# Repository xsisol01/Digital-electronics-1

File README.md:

# Digital-electronics-1
## Labs
*hello hello*
~~chyba~~

Meno|Priezvisko
------- | -------
Filip|Sisolak

**Source code**

```vhdl
architecture data flow 
```

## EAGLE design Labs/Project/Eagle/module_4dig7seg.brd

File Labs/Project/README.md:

# Door lock system with PIN (4-digit) terminal, 4x3 push buttons, 4-digit 7-segment display, relay for door lock control.

### Team members
* Bohuslav Šotola
* Tomáš Škurla
* Barbora Šimková
* Filip Šišolák

Github repository link : https://github.com/xsisol01/Digital-electronics-1/tree/main/Labs

### Project objectives
The scope of this project was to create the lock system utilizing an Arty A7-100T board. The project, as per the initial assignment, consists of a 4x3 keypad, a 4-digit 7segment display, and a relay to control the door lock. We also implemented a Three-color-LED whose colors represent each state of the door ( Green for Opened, Red for Closed). The 4-digit 7 segment display is located on a breadboard connected to the board via Pmod connectors.

### Hardware description
Hardware used in this project:
* Arty A7-100T board (https://www.robotshop.com/eu/en/arty-a7-100t-artix-7-fpga-development-board.html)
* Pmod SSR: Solid State Relay Electronic Switch (https://store.digilentinc.com/pmod-ssr-solid-state-relay-electronic-switch/)
* Membrane 3x4 Matrix Keypad (https://www.adafruit.com/product/419)
* Custom 4 Digit 7 segment module 

#### Table with pinouts for used modules
##### Table for Keypad control module
| General purpose I/O pins | 
|      :--------:          | 
|    I40     | 
|    I39     | 
|    I38     | 
|    I37     | 
|    I36     | 
|    I35     | 
|    I34     | 
##### Table for 7 seg 4 digits module 
| Pmod JB | Connection | Cathodes | Pmod JC | Connection | Anodes |
| :-----: | :--------: | :------: | :-----: | :--------: | :----: |
|  Pin 1  |    E15     |    CA    |  Pin 1  |    U12     |  AN0   |
|  Pin 2  |    E16     |    CB    |  Pin 2  |    V12     |  AN1   |
|  Pin 3  |    D15     |    CC    |  Pin 3  |    V10     |  AN2   |
|  Pin 4  |    C15     |    CD    |  Pin 4  |    V11     |  AN3   |
|  Pin 7  |    J17     |    CE    |  Pin 7  |    U14     |   -    |
|  Pin 8  |    J18     |    CF    |  Pin 8  |    V14     |   -    |
|  Pin 9  |    K15     |    CG    |  Pin 9  |    T13     |   -    |
| Pin 10  |    J15     |    DP    | Pin 10  |    U13     |   -    |

##### Table for Relay module
| Pmod JA | Connection | 
| :-----: | :--------: | 
|  Pin 1  |    G13     | 
|  Pin 2  |    B11     | 
|  Pin 3  |    A11     | 
|  Pin 4  |    D12     | 
|  Pin 7  |    D13     | 
|  Pin 8  |    B18     | 
|  Pin 9  |    A18     | 
| Pin 10  |    K16     | 

#### Theoretical imagine of all of modules connected together 

### VHDL modules description and simulations
* [4x3 KeyPad control module](https://github.com/xsisol01/Digital-electronics-1/tree/main/Labs/Project#keypad-control-module) 
* [Relay control module](https://github.com/xsisol01/Digital-electronics-1/tree/main/Labs/Project#relay-control-module)
* [7seg display control module](https://github.com/xsisol01/Digital-electronics-1/tree/main/Labs/Project#driver-for-multiple-seven-segment-displays)
* [Lock logic module](https://github.com/xsisol01/Digital-electronics-1/tree/main/Labs/Project#lock-logic-module)
* [Top module](https://github.com/xsisol01/Digital-electronics-1/tree/main/Labs/Project#top-module-description-and-simulations)

## KeyPad control module
### Description
Module "keypad_to_num" for controlling 4x3 keypad contains from 3 input ports -> clk (needed to control state machine), reset (which is not needed in this case, but we are using template from previous labs), row_i (where comes the inforamtion which key was pressed). There are also 2 output ports -> col_o (sending sequention of 0 and 1 to the keypad columns) and finally the num_o (which send bin signal representing pressed key on keypad).
Keypad_to_num works on basis of state machine where each state change to another after defined time.
Each key represent bin signal - same as the label of the button on keypad for example 7 means b"0111". All other combinations are in table.

##### Functionality 

##### Table - Key pressed on keypad => num_o
| Key | num_o | Value |
| :-: | :-: | :-: | 
| 0 | b"0000" | 0 | 
| 1 | b"0001" | 1 | 
| 2 | b"0010" | 2 | 
| 3 | b"0011" | 3 | 
| 4 | b"0100" | 4 | 
| 5 | b"0101" | 5 | 
| 6 | b"0110" | 6 | 
| 7 | b"0111" | 7 | 
| 8 | b"1000" | 8 |  
| 9 | b"1001" | 9 | 
| * | b"1110" | DELETE | 
| # | b"1111" | ENTER |
| N/A | b"1101" | DEFAULT | 

##### State diagram 

### VHDL code and simulation
##### VHDL code of KeyPad controller - `keypad_to_num.vhdl`
[Link to `keypad_to_num.vhdl`](https://github.com/xsisol01/Digital-electronics-1/blob/main/Labs/Project/Lock/project_final2.srcs/sources_1/imports/Project/Project_lock/Project_lock.srcs/sources_1/new/keypad_to_num.vhd)

```vhdl
library ieee;
use ieee.std_logic_1164.all;
use ieee.numeric_std.all;

------------------------------------------------------------------------
-- Entity declaration for traffic light controller
------------------------------------------------------------------------
entity keypad_to_num is
    port(
        clk         : in  std_logic;
        reset       : in  std_logic;
        row_i       : in  std_logic_vector(4 - 1 downto 0);     -- input from keypad
        
        col_o       : out std_logic_vector(3 - 1 downto 0);     -- output to keypad
        num_o       : out std_logic_vector(4 - 1 downto 0)      --Output signal with 4bit number 0-9, enter, delete
        
    );
end entity keypad_to_num;

------------------------------------------------------------------------
-- Architecture declaration for traffic light controller
------------------------------------------------------------------------
architecture Behavioral of keypad_to_num is

    -- Define the states
    type t_state is (SET_COLH,      --after reset
                     SET_COL1,
                     SET_COL2,
                     SET_COL3
                     );
        
    -- Define the signal that uses different states
    signal s_state  : t_state;
    -- Internal clock enable
    signal s_en     : std_logic; --not needed in this case
    -- Local delay counter
    signal   s_cnt  : unsigned(5 - 1 downto 0);

    constant c_DELAY_100ms : unsigned(5 - 1 downto 0) := b"0_0010"; --one pulse every 100ms
    constant c_ZERO        : unsigned(5 - 1 downto 0) := b"0_0000";

begin

    clk_en0 : entity work.clock_enable
        generic map(
            g_MAX => 5000000       -- g_MAX = 50 ms / (1/100 MHz) 
        )
        port map(
            clk   => clk,
            reset => reset,
            ce_o  => s_en
        );

    --Process sensitive to clock change, defining state machine rules
    p_in_to_num_out : process(clk)
    begin
        if rising_edge(clk) then
            if (reset = '1') then          -- Synchronous reset
                s_state <= SET_COLH ;      -- Set initial state
                --s_cnt <= c_ZERO;

            elsif (s_en = '1') then
            
                case s_state is
                    when SET_COLH =>
                        if (s_cnt < c_DELAY_100ms) then
                            s_cnt <= s_cnt + 1;   
                        else
                            s_state <= SET_COL1;
                            s_cnt <= c_ZERO;
                        end if;
                        
                    when SET_COL1 =>
                        if (s_cnt < c_DELAY_100ms) then
                            s_cnt <= s_cnt + 1;
                        else
                            s_state <= SET_COL2;
                            s_cnt <= c_ZERO;
                       end if;
                           
                    when SET_COL2 =>
                        if (s_cnt < c_DELAY_100ms) then
                            s_cnt <= s_cnt + 1; 
                        else
                            s_state <= SET_COL3;
                            s_cnt <= c_ZERO;
                        end if;
                        
                    when SET_COL3 =>
                        if (s_cnt < c_DELAY_100ms) then
                            s_cnt <= s_cnt + 1; 
                        else
                            s_state <= SET_COL1;
                            s_cnt <= c_ZERO;
                        end if; 
                           
                    when others =>
                        s_state <= SET_COLH;                   
               end case;            
            end if; -- Synchronous reset
        end if; -- Rising edge
    end process p_in_to_num_out;

    --Process senstitive on current state and setting output to columns
    p_output_statechanger : process(s_state)
    begin
        case s_state is
            when SET_COLH =>
                col_o <= "111";   
            when SET_COL1 =>
                col_o <= "011";    
            when SET_COL2 =>
                col_o <= "101";     
            when SET_COL3 =>
                col_o <= "110";
            when others =>
                col_o <= "111";
        end case;
    end process p_output_statechanger;

    --Process sensitive to row_i changes and setting output based on current state
    p_output_row_check_out : process(row_i)
    begin
        case s_state is
            when SET_COLH =>
                num_o <= "1101";                -- default
                
            when SET_COL1 =>
                if(row_i = "0111") then
                    num_o <= "0001";            --set output 1 - pressed
                               
                elsif(row_i = "1011") then  
                    num_o <= "0100";            --set output 4 - pressed
                                
                elsif(row_i = "1101") then  
                    num_o <= "0111";            --set output 7 - pressed  
                                
                elsif(row_i = "1110") then  
                    num_o <= "1110";            --set output *(delete) - pressed
                else 
                    num_o <= "1101";            --defult            
                end if;
                
            when SET_COL2 =>
                if(row_i = "0111") then
                    num_o <= "0010";            --set output 2 - pressed
                            
                elsif(row_i = "1011") then  
                    num_o <= "0101";            --set output 5 - pressed
                            
                elsif(row_i = "1101") then  
                     num_o <= "1000";           --set output 8 - pressed  
                            
                elsif(row_i = "1110") then  
                     num_o <= "0000";           --set output 0 - pressed 
                else 
                     num_o <= "1101";           --defult no output          
                end if;
                
            when SET_COL3 =>
                if(row_i = "0111") then
                     num_o <= "0011";           --set output 3 - pressed
                                
                elsif(row_i = "1011") then  
                     num_o <= "0110";           --set output 6 - pressed
                                
                elsif(row_i = "1101") then  
                       num_o <= "1001";         --set output 9 - pressed  
                                
                elsif(row_i = "1110") then  
                       num_o <= "1111";         --set output #(enter) - pressed
                else 
                     num_o <= "1101";           --defult         
                end if; 
                
            when others =>
                num_o <= "1101";
          end case;
      end process p_output_row_check_out;  
end architecture Behavioral;
```

##### Simulation of KeyPad controller - `tb_keypad_to_num.vhdl`
[Link to `tb_keypad_to_num.vhdl`](https://github.com/xsisol01/Digital-electronics-1/blob/main/Labs/Project/Lock/project_final2.srcs/sim_1/new/tb_keypad_to_num.vhd)

```vhdl
library ieee;
use ieee.std_logic_1164.all;

entity tb_keypad_to_num is
    -- Entity of testbench is always empty
end entity tb_keypad_to_num;

architecture testbench of tb_keypad_to_num is

    -- Local constants
    constant c_CLK_100MHZ_PERIOD : time := 10 ns;

    --Local signals
    signal s_clk_100MHz : std_logic;
    signal s_reset      : std_logic;
    signal s_row        : std_logic_vector(4 - 1 downto 0);
    signal s_col        : std_logic_vector(3 - 1 downto 0);
    signal s_num        : std_logic_vector(4 - 1 downto 0);

begin

    uut_tlc : entity work.keypad_to_num
        port map(
            clk     => s_clk_100MHz,
            reset   => s_reset, 
            row_i   => s_row,
            col_o   => s_col,
            num_o   => s_num
        );

    p_clk_gen : process
    begin
        while now < 800 ms loop   
            s_clk_100MHz <= '0';
            wait for c_CLK_100MHZ_PERIOD / 2;
            s_clk_100MHz <= '1';
            wait for c_CLK_100MHZ_PERIOD / 2;
        end loop;
        wait;
    end process p_clk_gen;

    p_stimulus : process
    begin
    
        s_row <= "1111";  
        wait for 57 ms;
    
        s_row <= "0111";
        wait for 50 ms; 
        
        s_row <= "1111";  
        wait for 157 ms; 
        
        s_row <= "1101";
        wait for 52 ms;
        
        s_row <= "1111";  
        wait for 157 ms; 
        
        s_row <= "1011";
        wait for 52 ms;

        s_row <= "1111";  
        wait;
    end process p_stimulus;

end architecture testbench;  
```

##### Image of simulation waveforms - simulating KeyPad controller module

## Relay control module
### Description
In this project there is also a solid state relay which is connected to the board via Pmod (JA) connectors. I use a two – state diagram: Close_door (default state) and Open_door.

If keypad_i = ‘1’ the Close_door will be changed to state Open_door. Signal s_keypad is coming from module locker_logic.

If keypad_i = ‘0’ the Close_door will be still closed.

Solid state relay uses six pins, but only three are used, namely: Pin 1 (ON), Pin 5 (GND) and Pin 6 (VCC  3.3/5V).

STATES:

Open_door:

door_o = ‘1’  //door is opened

LED_o = “010” // LED color is green

Close_door:

door_o = ‘0’  //door is closed

LED_o = “100”// LED color is red

### Functionality 

### State Diagram

### VHDL code and simulation
#### VHDL code of Relay controller - `relay_to_door.vhdl`
[Link to `relay_to_door.vhdl`](https://github.com/xsisol01/Digital-electronics-1/blob/main/Labs/Project/Lock/project_final2.srcs/sources_1/new/relay_to_door.vhd)

```vhdl
library ieee;
use ieee.std_logic_1164.all;
use ieee.numeric_std.all;

entity relay_to_door is
    port(
       keypad_i     : in  std_logic;
        clk          : in  std_logic;
        reset        : in  std_logic;
        
        door_o      : out  std_logic; 
        LED_o : out std_logic_vector(3 - 1 downto 0)

    );
end entity relay_to_door;

architecture Behavioral of relay_to_door is

    type   t_state is (close_door, open_door);                   
    signal s_state  : t_state;

    signal s_en             : std_logic;
    signal s_keypad         : std_logic;

    signal   s_cnt  : unsigned(5 - 1 downto 0);

    constant c_DELAY_7SEC : unsigned(5 - 1 downto 0) := b"1_1100";
    constant c_DELAY_3SEC : unsigned(5 - 1 downto 0) := b"0_1100";
    constant c_DELAY_1SEC : unsigned(5 - 1 downto 0) := b"0_0100";
    constant c_ZERO       : unsigned(5 - 1 downto 0) := b"0_0000";

begin
    
    s_en <= '1';

 p_state_changer : process(clk,reset,keypad_i)
    begin
        if rising_edge(clk) then
            if (reset = '1') then     
                s_state <= close_door ;     
                s_cnt <= c_ZERO;

            elsif (s_en = '1') then
            
                case s_state is
                    when close_door =>
                        if (keypad_i = '1') then
                            s_state <= open_door;
                            s_cnt   <= c_ZERO;  
                        else
                            s_state <= close_door;
                            s_cnt <= c_ZERO;
                        end if;
                        
                    when open_door =>
                        if (s_cnt < c_DELAY_7SEC) then
                            s_cnt <= s_cnt + 1;
                        else
                            s_state <= close_door;
                            s_cnt <= c_ZERO;
                       end if;
                                  
                    when others =>
                        s_state <= close_door;                   
               end case;            
            end if;
        end if; 
    end process p_state_changer;

    p_output_door : process(s_state)
    begin
        case s_state is

            when close_door =>
                LED_o <= "100";
                door_o <='0';
                
            when open_door =>
                LED_o <= "010";   
                door_o <='1';
           
        end case;
    end process p_output_door;

end architecture Behavioral;

```

#### Simulation of Relay control - `tb_relay_to_door.vhdl`
[Link to `tb_relay_to_door.vhdl`](https://github.com/xsisol01/Digital-electronics-1/blob/main/Labs/Project/Lock/project_final2.srcs/sim_1/new/tb_relay_to_door.vhd)

```vhdl
library ieee;
use ieee.std_logic_1164.all;

entity tb_relay_to_door is
    -- Entity of testbench is always empty
end entity tb_relay_to_door;

architecture testbench of tb_relay_to_door is

    constant c_CLK_100MHZ_PERIOD : time := 10 ns;

    --Local signals
    signal s_clk_100MHz : std_logic;
    signal s_reset      : std_logic;
    signal s_keypad         : std_logic;
    
    signal s_LED      : std_logic_vector(3 - 1 downto 0);

begin
    uut_relay_to_door : entity work.relay_to_door
        port map(
            clk     => s_clk_100MHz,
            reset   => s_reset,
            keypad_i =>s_keypad,
            LED_o => s_LED

        );

    p_clk_gen : process
    begin
        while now < 10000 ns loop 
            s_clk_100MHz <= '0';
            wait for c_CLK_100MHZ_PERIOD / 2;
            s_clk_100MHz <= '1';
            wait for c_CLK_100MHZ_PERIOD / 2;
        end loop;
        wait;
    end process p_clk_gen;

    p_reset_gen : process
    begin
        s_reset <= '0';
        s_keypad <= '1'; wait for 200ns;
        s_keypad <= '0';wait for 100ns;
        s_keypad <= '1';
        wait;
    end process p_reset_gen;

    p_stimulus : process
    begin
        
        wait;
    end process p_stimulus;

end architecture testbench;

```
#### Image of simulation waveforms

## Driver for multiple seven-segment displays

### Description
This module is used to display the numbers (PIN code) which are entered into a keypad. Module contains inputs signal such as reset, clk a four 4-bit signals data0_i, data1_i, data2_i, data3_i. Output signals are 7-bit signal seg_o and 4-bit signal dig_o. The signal seg_o determines which segment is going to light and the signal dig_o determines on which digit. The design source `clock_enable` is used to generate the clock enable signal. The design source `cnt_up_down` is binary n-bit counter and is used to counting in either direction. The design source `hex_7seg` is decoder for common anode 7-segment display.
##### Schematic of `driver_7seg_4digits` with connection to 7 segment displays

##### Schematic of 7 segment displays with connection to Arty-A7-100T

##### Board for 7 segment displays

### VHDL code and simulation

##### VHDL code of driver for 7 segment displays - `driver_7seg_4digits.vhdl`
[Link to `driver_7seg_4digits.vhdl`](https://github.com/xsisol01/Digital-electronics-1/blob/main/Labs/Project/Lock/project_final2.srcs/sources_1/new/new/driver_7seg_4digits.vhd)

```vhdl
------------------------------------------------------------------------
--
-- Copyright (c) 2020 Tomas Fryza
-- Dept. of Radio Electronics, Brno University of Technology, Czechia
-- This work is licensed under the terms of the MIT license.
--
------------------------------------------------------------------------

library ieee;
use ieee.std_logic_1164.all;
use ieee.numeric_std.all;

------------------------------------------------------------------------
-- Entity declaration for display driver
------------------------------------------------------------------------
entity driver_7seg_4digits is
    port(
        clk     : in  std_logic;        -- Main clock
        reset   : in  std_logic;        -- Synchronous reset
        -- 4-bit input values for individual digits
        data0_i : in  std_logic_vector(4 - 1 downto 0);
        data1_i : in  std_logic_vector(4 - 1 downto 0);
        data2_i : in  std_logic_vector(4 - 1 downto 0);
        data3_i : in  std_logic_vector(4 - 1 downto 0);
        -- Cathode values for individual segments
        seg_o   : out std_logic_vector(7 - 1 downto 0);
        -- Common anode signals to individual displays
        dig_o   : out std_logic_vector(4 - 1 downto 0)
    );
end entity driver_7seg_4digits;

------------------------------------------------------------------------
-- Architecture declaration for display driver
------------------------------------------------------------------------
architecture Behavioral of driver_7seg_4digits is

    -- Internal clock enable
    signal s_en  : std_logic;
    -- Internal 2-bit counter for multiplexing 4 digits
    signal s_cnt : std_logic_vector(2 - 1 downto 0);
    -- Internal 4-bit value for 7-segment decoder
    signal s_hex : std_logic_vector(4 - 1 downto 0);

begin
    --------------------------------------------------------------------
    -- Instance (copy) of clock_enable entity generates an enable pulse
    -- every 4 ms
    clk_en0 : entity work.clock_enable
        generic map(
        g_MAX => 4
        )
        port map(
         clk    => clk, 
         reset  => reset,
         ce_o   => s_en 
        );

    --------------------------------------------------------------------
    -- Instance (copy) of cnt_up_down entity performs a 2-bit down
    -- counter
    bin_cnt0 : entity work.cnt_up_down
        generic map(
        g_CNT_WIDTH => 2
        )
        port map(
        clk         => clk,   
        reset       => reset,   
        en_i        => s_en,  
        cnt_up_i    => '0',
        cnt_o       => s_cnt
        );

    --------------------------------------------------------------------
    -- Instance (copy) of hex_7seg entity performs a 7-segment display
    -- decoder
    hex2seg : entity work.hex_7seg
        port map(
            hex_i => s_hex,
            seg_o => seg_o
        );

    --------------------------------------------------------------------
    -- p_mux:
    -- A combinational process that implements a multiplexer for
    -- selecting data for a single digit, a decimal point signal, and 
    -- switches the common anodes of each display.
    --------------------------------------------------------------------
    p_mux : process(s_cnt, data0_i, data1_i, data2_i, data3_i)
    begin
        case s_cnt is
            when "11" =>
                s_hex <= data3_i;
                dig_o <= "0111";

            when "10" =>
                s_hex <= data2_i;
                dig_o <= "1011";

            when "01" =>
                s_hex <= data1_i;
                dig_o <= "1101";

            when others =>
                s_hex <= data0_i;
                dig_o <= "1110";
        end case;
    end process p_mux;

end architecture Behavioral;
```
##### VHDL code of testbench - `tb_driver_7seg_4digits.vhdl`
[Link to `tb_driver_7seg_4digits.vhdl`](https://github.com/xsisol01/Digital-electronics-1/blob/main/Labs/Project/Lock/project_final2.srcs/sim_1/new/tb_driver_7seg_4digits.vhd)
```vhdl
------------------------------------------------------------------------
--
-- Template for 4-digit 7-segment display driver testbench.
-- Nexys A7-50T, Vivado v2020.1.1, EDA Playground
--
-- Copyright (c) 2020 Tomas Fryza
-- Dept. of Radio Electronics, Brno University of Technology, Czechia
-- This work is licensed under the terms of the MIT license.
--
------------------------------------------------------------------------

library ieee;
use ieee.std_logic_1164.all;

------------------------------------------------------------------------
-- Entity declaration for testbench
------------------------------------------------------------------------
entity tb_driver_7seg_4digits is
    -- Entity of testbench is always empty
end entity tb_driver_7seg_4digits;

------------------------------------------------------------------------
-- Architecture body for testbench
------------------------------------------------------------------------
architecture testbench of tb_driver_7seg_4digits is

    -- Local constants
    constant c_CLK_100MHZ_PERIOD : time    := 10 ns;

    --Local signals
    signal s_clk_100MHz   : std_logic;
    signal s_reset        : std_logic;
    signal s_data0_i      : std_logic_vector(4 - 1 downto 0);
    signal s_data1_i      : std_logic_vector(4 - 1 downto 0);
    signal s_data2_i      : std_logic_vector(4 - 1 downto 0);
    signal s_data3_i      : std_logic_vector(4 - 1 downto 0);     
    signal s_seg_o        : std_logic_vector(7 - 1 downto 0);  
    signal s_dig_o        : std_logic_vector(4 - 1 downto 0);   

begin
    -- Connecting testbench signals with driver_7seg_4digits entity
    -- (Unit Under Test)
    uut_driver_7seg : entity work.driver_7seg_4digits
        port map (
        clk         => s_clk_100MHz,
        reset       => s_reset,
        data0_i     => s_data0_i,
        data1_i     => s_data1_i,
        data2_i     => s_data2_i,
        data3_i     => s_data3_i,  
        seg_o       => s_seg_o,
        dig_o       => s_dig_o
        );
        
    --------------------------------------------------------------------
    -- Clock generation process
    --------------------------------------------------------------------
    p_clk_gen : process
    begin
        while now < 750 ns loop         -- 75 periods of 100MHz clock
            s_clk_100MHz <= '0';
            wait for c_CLK_100MHZ_PERIOD / 2;
            s_clk_100MHz <= '1';
            wait for c_CLK_100MHZ_PERIOD / 2;
        end loop;
        wait;
    end process p_clk_gen;

    --------------------------------------------------------------------
    -- Reset generation process
    --------------------------------------------------------------------
     p_reset_gen : process
    begin
        s_reset <= '0';
        wait for 10 ns;
        
        -- Reset activated
        s_reset <= '1';
        wait for 53 ns;

        s_reset <= '0';
        wait;
    end process p_reset_gen;

    --------------------------------------------------------------------
    -- Data generation process
    --------------------------------------------------------------------
    p_stimulus : process
    begin
        report "Stimulus process started" severity note;
        
        s_data3_i <= "0011";
        s_data2_i <= "0001";   
        s_data1_i <= "0100";
        s_data0_i <= "0010";
        
        wait for 600 ns;
            -- Expected output
        	assert ((s_seg_o = "0000110") and (s_dig_o = "0111"))
        	-- If false, then report an error
        	report "Test failed for input on 600ns" severity error;
        
        s_data3_i <= "0000";
        s_data2_i <= "0001";   
        s_data1_i <= "0000";
        s_data0_i <= "0001";
        
        wait for 150 ns;
            -- Expected output
        	assert ((s_seg_o = "1001111") and (s_dig_o = "1110"))
        	-- If false, then report an error
        	report "Test failed for input on 750ns" severity error;
        	
        s_data3_i <= "0001";
        s_data2_i <= "0010";   
        s_data1_i <= "0011";
        s_data0_i <= "0100";

        report "Stimulus process finished" severity note;
        wait;
    end process p_stimulus;

end architecture testbench;
```

##### Decoder truth table for common anode 7-segment display:

| **Hex** | **Inputs** | **A** | **B** | **C** | **D** | **E** | **F** | **G** |
| :-: | :-: | :-: | :-: | :-: | :-: | :-: | :-: | :-: |
| 0 | 0000 | 0 | 0 | 0 | 0 | 0 | 0 | 1 |
| 1 | 0001 | 1 | 0 | 0 | 1 | 1 | 1 | 1 |
| 2 | 0010 | 0 | 0 | 1 | 0 | 0 | 1 | 0 |
| 3 | 0011 | 0 | 0 | 0 | 0 | 1 | 1 | 0 |
| 4 | 0100 | 1 | 0 | 0 | 1 | 1 | 0 | 0 |
| 5 | 0101 | 0 | 1 | 0 | 0 | 1 | 0 | 0 |
| 6 | 0110 | 0 | 1 | 0 | 0 | 0 | 0 | 0 |
| 7 | 0111 | 0 | 0 | 0 | 1 | 1 | 1 | 1 |
| 8 | 1000 | 0 | 0 | 0 | 0 | 0 | 0 | 0 |
| 9 | 1001 | 0 | 0 | 0 | 0 | 1 | 0 | 0 |
| A | 1010 | 0 | 0 | 0 | 1 | 0 | 0 | 0 |
| b | 1011 | 1 | 1 | 0 | 0 | 0 | 0 | 0 |
| C | 1100 | 0 | 1 | 1 | 0 | 0 | 0 | 1 |
| d | 1101 | 1 | 1 | 1 | 1 | 1 | 1 | 1 |
| E | 1110 | 0 | 1 | 1 | 0 | 0 | 0 | 0 |
| F | 1111 | 0 | 1 | 1 | 1 | 0 | 0 | 0 |

##### VHDL code of decoder to 7 segment display  - `hex_7seg.vhdl`
[Link to `hex_7seg.vhdl`](https://github.com/xsisol01/Digital-electronics-1/blob/main/Labs/Project/Lock/project_final2.srcs/sources_1/new/new/hex_7seg.vhd)
```vhdl
----------------------------------------------------------------------------------
-- Company: 
-- Engineer: 
-- 
-- Create Date: 03.03.2021 13:13:50
-- Design Name: 
-- Module Name: hex_7seg - Behavioral
-- Project Name: 
-- Target Devices: 
-- Tool Versions: 
-- Description: 
-- 
-- Dependencies: 
-- 
-- Revision:
-- Revision 0.01 - File Created
-- Additional Comments:
-- 
----------------------------------------------------------------------------------

library IEEE;
use IEEE.STD_LOGIC_1164.ALL;

-- Uncomment the following library declaration if using
-- arithmetic functions with Signed or Unsigned values
--use IEEE.NUMERIC_STD.ALL;

-- Uncomment the following library declaration if instantiating
-- any Xilinx leaf cells in this code.
--library UNISIM;
--use UNISIM.VComponents.all;

entity hex_7seg is
    Port ( 
        hex_i : in STD_LOGIC_VECTOR (4 - 1 downto 0);
        seg_o : out STD_LOGIC_VECTOR (7 - 1 downto 0)
        );
end hex_7seg;

architecture Behavioral of hex_7seg is

begin

    --------------------------------------------------------------------
    -- p_7seg_decoder:
    -- A combinational process for 7-segment display decoder. 
    -- Any time "hex_i" is changed, the process is "executed".
    -- Output pin seg_o(6) corresponds to segment A, seg_o(5) to B, etc.
    --------------------------------------------------------------------
    
    p_7seg_decoder : process(hex_i)
    begin
        case hex_i is
            when "0000" =>
                seg_o <= "0000001";     -- 0
            when "0001" =>
                seg_o <= "1001111";     -- 1
             when "0010" =>
                seg_o <= "0010010";     -- 2
             when "0011" =>
                seg_o <= "0000110";     -- 3
             when "0100" =>
                seg_o <= "1001100";     -- 4
             when "0101" =>
                seg_o <= "0100100";     -- 5
             when "0110" =>
                seg_o <= "0100000";     -- 6
             when "0111" =>
                seg_o <= "0001111";     -- 7  
             when "1000" =>
                seg_o <= "0000000";     -- 8
             when "1001" =>
                seg_o <= "0000100";     -- 9
             when "1010" =>
                seg_o <= "0001000";     -- A
             when "1011" =>
                seg_o <= "1100000";     -- b
             when "1100" =>
                seg_o <= "0110001";     -- C
             when "1101" =>
                seg_o <= "1111111";     -- d
            when "1110" =>
                seg_o <= "0110000";     -- E
            when others =>
                seg_o <= "0111000";     -- F
        end case;
    end process p_7seg_decoder;

end Behavioral;

```

##### VHDL code of `clock_enable.vhdl`
[Link to `clock_enable.vhdl`](https://github.com/xsisol01/Digital-electronics-1/blob/main/Labs/Project/Lock/project_final2.srcs/sources_1/new/new/clock_enable.vhd)

```vhdl
------------------------------------------------------------------------
--
-- Generates clock enable signal.
-- Nexys A7-50T, Vivado v2020.1.1, EDA Playground
--
-- Copyright (c) 2019-Present Tomas Fryza
-- Dept. of Radio Electronics, Brno University of Technology, Czechia
-- This work is licensed under the terms of the MIT license.
--
------------------------------------------------------------------------

library ieee;               -- Standard library
use ieee.std_logic_1164.all;-- Package for data types and logic operations
use ieee.numeric_std.all;   -- Package for arithmetic operations

------------------------------------------------------------------------
-- Entity declaration for clock enable
------------------------------------------------------------------------
entity clock_enable is
    generic(
        g_MAX : natural := 30       -- Number of clk pulses to generate
                                    -- one enable signal period
    );  -- Note that there IS a semicolon between generic and port
        -- sections
    port(
        clk   : in  std_logic;      -- Main clock
        reset : in  std_logic;      -- Synchronous reset
        ce_o  : out std_logic       -- Clock enable pulse signal
    );
end entity clock_enable;

------------------------------------------------------------------------
-- Architecture body for clock enable
------------------------------------------------------------------------
architecture Behavioral of clock_enable is

    -- Local counter
    signal s_cnt_local : natural;

begin
    --------------------------------------------------------------------
    -- p_clk_ena:
    -- Generate clock enable signal. By default, enable signal is low 
    -- and generated pulse is always one clock long.
    --------------------------------------------------------------------
    p_clk_ena : process(clk)
    begin
        if rising_edge(clk) then        -- Synchronous process

            if (reset = '1') then       -- High active reset
                s_cnt_local <= 0;       -- Clear local counter
                ce_o        <= '0';     -- Set output to low

            -- Test number of clock periods
            elsif (s_cnt_local >= (g_MAX - 1)) then
                s_cnt_local <= 0;       -- Clear local counter
                ce_o        <= '1';     -- Generate clock enable pulse

            else
                s_cnt_local <= s_cnt_local + 1;
                ce_o        <= '0';
            end if;
        end if;
    end process p_clk_ena;

end architecture Behavioral;
```

##### VHDL code of `cnt_up_down.vhdl`
[Link to `cnt_up_down.vhdl`](https://github.com/xsisol01/Digital-electronics-1/blob/main/Labs/Project/Lock/project_final2.srcs/sources_1/new/new/cnt_up_down.vhd)
```vhdl
------------------------------------------------------------------------
--
-- N-bit Up/Down binary counter.
-- Nexys A7-50T, Vivado v2020.1.1, EDA Playground
--
-- Copyright (c) 2019-Present Tomas Fryza
-- Dept. of Radio Electronics, Brno University of Technology, Czechia
-- This work is licensed under the terms of the MIT license.
--
------------------------------------------------------------------------

library ieee;
use ieee.std_logic_1164.all;
use ieee.numeric_std.all;

------------------------------------------------------------------------
-- Entity declaration for n-bit counter
------------------------------------------------------------------------
entity cnt_up_down is
    generic(
        g_CNT_WIDTH : natural := 4      -- Number of bits for counter
    );
    port(
        clk      : in  std_logic;       -- Main clock
        reset    : in  std_logic;       -- Synchronous reset
        en_i     : in  std_logic;       -- Enable input
        cnt_up_i : in  std_logic;       -- Direction of the counter
        cnt_o    : out std_logic_vector(g_CNT_WIDTH - 1 downto 0)
    );
end entity cnt_up_down;

------------------------------------------------------------------------
-- Architecture body for n-bit counter
------------------------------------------------------------------------
architecture behavioral of cnt_up_down is

    -- Local counter
    signal s_cnt_local : unsigned(g_CNT_WIDTH - 1 downto 0);

begin
    --------------------------------------------------------------------
    -- p_cnt_up_down:
    -- Clocked process with synchronous reset which implements n-bit 
    -- up/down counter.
    --------------------------------------------------------------------
    p_cnt_up_down : process(clk)
    begin
        if rising_edge(clk) then
        
            if (reset = '1') then               -- Synchronous reset
                s_cnt_local <= (others => '0'); -- Clear all bits

            elsif (en_i = '1') then       -- Test if counter is enabled

                -- TEST COUNTER DIRECTION HERE
                if(cnt_up_i = '1') then
                     s_cnt_local <= s_cnt_local + 1;
                else
                     s_cnt_local <= s_cnt_local -1;
                end if;
            end if;
        end if;
    end process p_cnt_up_down;

    -- Output must be retyped from "unsigned" to "std_logic_vector"
    cnt_o <= std_logic_vector(s_cnt_local);

end architecture behavioral;

```
##### Simulation of `driver_7seg_4digits.vhdl`

### Lock logic module
##### Description
Module "locker_logic" is the main part of the lock. Module contains from 3 input ports -> clk (needed to control state machine), reset and num_i ( where comes signal with information which button was pressed on keypad). It also contain 5 ouput ports where 4 of them are data0_o-data3_0 (those ports sends signals what to show on displays to driver 7seg) and the last output port is relay_o ( which send '1' to relay module if Password is selected correctly).
Password is set to 1234 as we can see in code constants NUM(1-4)_PW. Lock logic works on principle of state machine, where next state comes after pushing another button on keypad.
Checking if the numbers were selected correctly, we are working with defined signals signal "s_num(1-4)_corr". These signals are setted to '1' when the pressed button was same as constant NUMx_PW.

##### Block scheme

##### State diagram

##### VHDL code of Lock logic module - `locker_logic.vhdl`
[Link to `locker_logic.vhdl`](https://github.com/xsisol01/Digital-electronics-1/blob/main/Labs/Project/Lock/project_final2.srcs/sources_1/imports/Project/Final/Nov%20prieinok/try/try.srcs/sources_1/new/locker_logic.vhd)

```vhdl
library IEEE;
use IEEE.STD_LOGIC_1164.ALL;
use ieee.numeric_std.all;

-- Uncomment the following library declaration if using
-- arithmetic functions with Signed or Unsigned values
--use IEEE.NUMERIC_STD.ALL;

-- Uncomment the following library declaration if instantiating
-- any Xilinx leaf cells in this code.
--library UNISIM;
--use UNISIM.VComponents.all;

entity locker_logic is
    Port (
        clk         : in std_logic;
        reset       : in std_logic;
        num_i       : in std_logic_vector( 4 - 1 downto 0);     -- input value from keypad controler
         
        data0_o     : out std_logic_vector( 4 - 1 downto 0);    --output value for 1st display of 4dig 7 segment module
        data1_o     : out std_logic_vector( 4 - 1 downto 0);    --output value for 2nd display of 4dig 7 segment module
        data2_o     : out std_logic_vector( 4 - 1 downto 0);    --output value for 3rd display of 4dig 7 segment module
        data3_o     : out std_logic_vector( 4 - 1 downto 0);    --output value for 4th display of 4dig 7 segment module
        
        relay_o     : out std_logic     -- value 1/0 for relay module to open/lock
     );
end locker_logic;

architecture Behavioral of locker_logic is

    -- define the password, for this case PW is 1234 
    constant NUM1_PW : std_logic_vector(4 - 1 downto 0) := "0001";
    constant NUM2_PW : std_logic_vector(4 - 1 downto 0) := "0010";
    constant NUM3_PW : std_logic_vector(4 - 1 downto 0) := "0011";
    constant NUM4_PW : std_logic_vector(4 - 1 downto 0) := "0100";
    
    -- State definition
    -------------------------------
    type t_stateLO is ( LOCKED,
                        OPENED
                       );
                       
    type t_stateNUM is (NUM0, -- after reset
                        NUM1,
                        NUM2,
                        NUM3,
                        NUM4
                        
                       );
                       
    -- Define the signals that uses different states                   
    signal s_stateLO            : t_stateLO;
    signal s_stateNUM           : t_stateNUM;
    
    -- Signal for pw reset 
    signal s_password_reset     : std_logic;
  
    -- signals which are setted to '1' after correct number selected
    signal s_num1_corr      : std_logic;
    signal s_num2_corr      : std_logic;
    signal s_num3_corr      : std_logic;
    signal s_num4_corr      : std_logic;
    
    -- signals wich number was selected
    signal s_num1_displ     : std_logic_vector( 4 - 1 downto 0);
    signal s_num2_displ     : std_logic_vector( 4 - 1 downto 0);
    signal s_num3_displ     : std_logic_vector( 4 - 1 downto 0);
    signal s_num4_displ     : std_logic_vector( 4 - 1 downto 0);
       
begin

    clk_en0 : entity work.clock_enable
        generic map(
            g_MAX => 5000000       -- g_MAX = 50 ms / (1/100 MHz) 
        )
        port map(
            clk   => clk,
            reset => reset   
        );

    -- process sensitive to num_i, reset, s_password_reset changes
    -- changing states
    p_stateNUM_changer : process(num_i,reset, s_password_reset)
    begin 
        if (s_password_reset = '1' or reset = '1') then 
            s_stateNUM <= NUM0;
            
            s_password_reset <= '0';
       else
            case s_stateNUM is
            
                when NUM0 =>                    --after reset 
                    if( num_i = "1101") then    -- when input from keypad is d - default staying in same state
                        s_stateNUM <= NUM0;                        
                    else                        -- else going to another
                        s_stateNUM <= NUM1;                           
                    end if;
                    
                when NUM1 =>
                    if( num_i = "1101") then
                        s_stateNUM <= NUM1;
                    else
                        s_stateNUM <= NUM2;                             
                    end if;
                    
                when NUM2 =>
                    if( num_i = "1101") then
                        s_stateNUM <= NUM2;
                    else  
                        s_stateNUM <= NUM3;                             
                    end if;
                    
                when NUM3 =>
                    if( num_i = "1101") then
                        s_stateNUM <= NUM3;
                    else
                        s_stateNUM <= NUM4;                             
                    end if;
                    
                when NUM4 =>
                    if( num_i = "1101") then
                        s_password_reset <= '1';    --auto reset after NUM4                           
                    end if;
          
                when others => 
                    s_stateNUM <= NUM0;             -- default state NUM0
            end case;  --stateNUM 
         end if;  
    end process p_stateNUM_changer;

    -- Process sensitive to s_stateNUM, s_num4_corr, s_num1_displ, s_num2_displ, s_num3_displ, s_num4_displ changes
    -- Checking if all numbers were selected corecctly and opening the relay
    -- Also working with display info
    p_correct_signal_changer : process (s_stateNUM, s_num4_corr, s_num1_displ, s_num2_displ, s_num3_displ, s_num4_displ)
    begin
        case s_stateNUM is 
        
           when NUM1 =>
               data3_o <= "1101";           -- defaultly giving output for display of previous state to default
               s_num1_displ <= num_i;       -- assigment of input information to signal 
               data0_o <= s_num1_displ;     -- ouputin input inforamtion to display 
               
               if(num_i = NUM1_PW) then 
                   s_num1_corr <= '1';    
               end if; 
               
           when NUM2 =>
               data0_o <= "1101";
               s_num2_displ <= num_i;
               data1_o <= s_num2_displ;
               
               if(num_i = NUM2_PW) then 
                   s_num2_corr <= '1';
                 
               end if; 
                    
           when NUM3 =>
               data1_o <= "1101";
               s_num3_displ <= num_i;
               data2_o <= s_num3_displ;
               
               if(num_i = NUM3_PW) then 
                   s_num3_corr <= '1';
               end if;
                   
           when NUM4 =>
               data2_o <= "1101";
               s_num4_displ <= num_i;
               data3_o <= s_num4_displ;
           
               if(num_i = NUM4_PW) then 
                   s_num4_corr <= '1';
                   if ( s_num1_corr = '1' and s_num2_corr = '1' and s_num3_corr = '1' and s_num4_corr = '1') then 
                       s_stateLO <= OPENED;
                   else
                       s_stateLO <= LOCKED;
                       
                   end if;
               end if;
    
          when others =>
               data0_o <= "1101";
               data1_o <= "1101";
               data2_o <= "1101";
               data3_o <= "1101";
               
               s_num1_displ <= "1101";
               s_num2_displ <= "1101";
               s_num3_displ <= "1101";
               s_num4_displ <= "1101";
               
               s_stateLO <= LOCKED;
               
               s_num1_corr <= '0';
               s_num2_corr <= '0';
               s_num3_corr <= '0';
               s_num4_corr <= '0';
            end case;

    end process p_correct_signal_changer;
    
    p_stateLO_defintion : process (clk)
    begin
        if rising_edge (clk) then
            case s_stateLO is 
            when LOCKED =>
                relay_o <= '0';
            when OPENED =>
                relay_o <= '1';
            when others =>
                relay_o <= '0';
            end case;
        end if;
    end process p_stateLO_defintion;
     
end Behavioral;
```

##### Simulation of lock logic - `tb_lock_logic.vhdl`
[Link to `tb_lock_logic.vhdl`](https://github.com/xsisol01/Digital-electronics-1/blob/main/Labs/Project/Lock/project_final2.srcs/sim_1/new/tb_lock_logic.vhd)

```vhdl
library IEEE;
use IEEE.STD_LOGIC_1164.ALL;
use ieee.numeric_std.all;

-- Uncomment the following library declaration if using
-- arithmetic functions with Signed or Unsigned values
--use IEEE.NUMERIC_STD.ALL;

-- Uncomment the following library declaration if instantiating
-- any Xilinx leaf cells in this code.
--library UNISIM;
--use UNISIM.VComponents.all;

entity tb_lock_logic is
--  Port ( );
end tb_lock_logic;
    
architecture testbench of tb_lock_logic is
    constant c_CLK_100MHZ_PERIOD : time := 1 ns;
    
    signal s_num    : std_logic_vector( 4 - 1 downto 0);
    signal s_reset  : std_logic; 
    signal s_clk_100MHZ : std_logic;
        
    signal s_data0  : std_logic_vector( 4 - 1 downto 0); 
    signal s_data1  : std_logic_vector( 4 - 1 downto 0);
    signal s_data2  : std_logic_vector( 4 - 1 downto 0); 
    signal s_data3  : std_logic_vector( 4 - 1 downto 0);
        
    signal s_relay  : std_logic;
begin
    
    uut_lock_logic  : entity work.locker_logic
        port map(
            num_i   => s_num,
            reset   => s_reset,
            data0_o => s_data0,
            data1_o => s_data1,
            data2_o => s_data2,
            data3_o => s_data3,
            relay_o => s_relay, 
            clk => s_CLK_100MHZ
        );

        p_clk_gen : process
    begin
        while now < 1000 ns loop   
            s_clk_100MHz <= '0';
            wait for c_CLK_100MHZ_PERIOD / 2;
            s_clk_100MHz <= '1';
            wait for c_CLK_100MHZ_PERIOD / 2;
        end loop;
        wait;
    end process p_clk_gen;
        
    p_stimulus : process
    begin
    
        s_num <= "1101";        --default keyboard output
        s_reset <= '1';
        wait for 14ns;
        
        s_reset <= '0';
        wait for 12ns;
        
        s_num <= "0001";        -- 1 to input
        wait for 12ns;
        
        s_num <= "1101";        --default keyboard output 
        wait for 20ns;
        
        s_num <= "0010";        -- 2 to input
        wait for 12ns;
        
        s_num <= "1101";        --default keyboard output
        wait for 20ns;
        
        s_num <= "0011";        -- 3 to input
        wait for 12ns;
        
        s_num <= "1101";        --default keyboard output
        wait for 20ns;
        
        s_num <= "0100";        -- 4 to input
        wait for 12ns;
        
        s_num <= "1101";        --default keyboard output
        wait for 26 ns;
                                --------- ALL numbers seted => again ---------      
        
        s_num <= "0111";        -- 7 to input
        wait for 12ns;
        
        s_num <= "1101";        --default keyboard output
        wait for 10ns;
        
        s_num <= "0101";        -- 5 to input
        wait for 12ns;
        
        s_num <= "1101";        --default keyboard output
        wait for 20ns;
        
        s_num <= "0011";        -- 3 to input 
        wait for 12ns;
        
        s_num <= "1101";        --default keyboard output
        wait for 20ns;
        
        s_num <= "0100";        -- 4 to input
        wait for 12ns;
        
        s_num <= "1101";        --default keyboard output
        wait;  
               
    end process p_stimulus;

end architecture testbench;
```
##### Image of simulation waveforms - simulating KeyPad controller module

## TOP module description and simulations

### Schematic of top

##### VHDL code of Top modul - `top.vhdl`
[Link to `top.vhdl`](https://github.com/xsisol01/Digital-electronics-1/blob/main/Labs/Project/Lock/project_final2.srcs/sources_1/new/top.vhd)

```vhdl
library IEEE;
use IEEE.STD_LOGIC_1164.ALL;

entity top is
  Port (
        CLK100MHZ    : in std_logic;
        ROW          : in std_logic_vector( 4 - 1 downto 0);
        SW           : in std_logic;
        
        COL          : out std_logic_vector( 3 - 1 downto 0);
        
        SEG_DISP     : out std_logic_vector ( 7 - 1 downto 0);
        
        DIG          : out std_logic_vector( 4 - 1 downto 0);
        LED          : out std_logic_vector( 3 - 1 downto 0);
        RELAY        : out std_logic

   );
end top;

architecture Behavioral of top is
    
    -- Signals to connect each module
    signal s_data0  : std_logic_vector( 4 - 1 downto 0);
    signal s_data1  : std_logic_vector( 4 - 1 downto 0);
    signal s_data2  : std_logic_vector( 4 - 1 downto 0);
    signal s_data3  : std_logic_vector( 4 - 1 downto 0);
    
    signal s_rel    : std_logic;
    signal s_num    : std_logic_vector ( 4 - 1 downto 0);
        
begin
    
    driver_seg_4 : entity work.driver_7seg_4digits
        port map(
            clk     => CLK100MHZ,
            reset   => SW,
            
            data0_i  => s_data0,
            data1_i  => s_data1,
            data2_i  => s_data2,
            data3_i  => s_data3,
            
            dig_o   => DIG,
            
            seg_o(6)   => SEG_DISP(6),
            seg_o(5)   => SEG_DISP(5),
            seg_o(4)   => SEG_DISP(4),
            seg_o(3)   => SEG_DISP(3),
            seg_o(2)   => SEG_DISP(2),
            seg_o(1)   => SEG_DISP(1),
            seg_o(0)   => SEG_DISP(0)   
        );
    
    keypad_to_num : entity work.keypad_to_num
        port map(
            clk     => CLK100MHZ,
            reset   => SW,
            
            col_o   => COL,
            row_i   => ROW,
            
            num_o   => s_num
        
        );
        
    locker_logic : entity work.locker_logic
        port map(
            clk     => CLK100MHZ,
            reset   => SW,
            
            num_i   => s_num,
            
            data0_o => s_data0,
            data1_o => s_data1, 
            data2_o => s_data2, 
            data3_o => s_data3, 
            
            relay_o => s_rel 
        
        );
        
     relay_to_door : entity work.relay_to_door
        port map(
            clk     => CLK100MHZ,
            reset   => SW,
            
            keypad_i => s_rel,
            
            LED_o   => LED,
            door_o  => RELAY
        
        );

end Behavioral;
```

##### Simulation top module - `tb_top.vhdl`
[Link to `tb_top.vhdl`](https://github.com/xsisol01/Digital-electronics-1/blob/main/Labs/Project/Lock/project_final2.srcs/sim_1/new/tb_top.vhd)

```vhdl
library IEEE;
use IEEE.STD_LOGIC_1164.ALL;

entity tb_top is
--  Port ( );
end tb_top;

architecture Behavioral of tb_top is

    constant c_CLK_100MHZ_PERIOD : time    := 10 ns;

    --Local signals
    signal s_clk_100MHz : std_logic;
    signal s_reset      : std_logic;
    signal s_col        :std_logic_vector(3-1 downto 0);
    
    signal s_row        :std_logic_vector( 4 - 1 downto 0);
    
    signal s_a        :std_logic;
    signal s_b        :std_logic;
    signal s_c        :std_logic;
    signal s_d        :std_logic;
    signal s_e        :std_logic;
    signal s_f        :std_logic;
    signal s_g        :std_logic;
    
    signal s_dig      :std_logic_vector(4-1 downto 0);
    
    signal s_led :std_logic_vector(3-1 downto 0);
    signal s_relay :std_logic;
    
begin

    uut_top : entity work.top
        port map(
            CLK100MHZ     => s_CLK_100MHz,
            SW   => s_reset,
            COL  => s_col,
            
            ROW  => s_row,
            
            SEG_DISP(6)  => s_a,
            SEG_DISP(5)   => s_b,
            SEG_DISP(4)   => s_c,
            SEG_DISP(3)   => s_d,
            SEG_DISP(2)   => s_e,
            SEG_DISP(1)   => s_f,
            SEG_DISP(0)   => s_g,
            
            DIG => s_dig,
            LED => s_led,
            RELAY => s_relay

        );

    --------------------------------------------------------------------
    -- Clock generation process
    --------------------------------------------------------------------
    p_clk_gen : process
    begin
        while now < 5 ms loop         
            s_clk_100MHz <= '0';
            wait for c_CLK_100MHZ_PERIOD / 2;
            s_clk_100MHz <= '1';
            wait for c_CLK_100MHZ_PERIOD / 2;
        end loop;
        wait;
    end process p_clk_gen;

p_stimulus : process
begin 

        s_reset <= '1';
        
        s_row <= "1111"; 
        wait for 26ns;
        s_reset <= '0'; 
        wait for 56ns;
    
        s_row <= "0111";
        wait for 65 ns; 
        
        s_row <= "1111";  
        wait for 56 ns; 
        
        s_row <= "0111";
        wait for 56 ns;
        
        s_row <= "1111";  
        wait for 57 ns; 
        
        s_row <= "0111";
        wait for 53 ns;
        
        s_row <= "1111";  
        wait for 70ns;
    
        s_row <= "1011";
        wait for 150 ns; 
        
        s_row <= "1111";  
        wait for 157 ns; 
        
        s_row <= "1101";
        wait for 152 ns;
        
        s_row <= "1111";  
        wait for 157 ns; 
        
        s_row <= "1011";
        wait for 152 ns;
        
        s_row <= "1111";  
        wait for 57 ns;
        
        s_row <= "1101";
        wait for 152 ns;
        
        s_row <= "1111";  
        wait for 157 ns; 
        
        s_row <= "1011";
        wait for 152 ns;

        s_row <= "1111";  
        wait;
end process p_stimulus;

end Behavioral;
```
##### Simulation waveform of top module

### Discussion of results
Our main goal was to fulfill the task, which we can say that we succeeded. In addition to entering, we wanted to implement delete and enter on the keyboard, which failed. On the other hand, we succeeded in implementing an LED indicator (red when close, green when open) and automatic locking of the lock after a certain time.

## Video

## References

   1. https://www.fpga4student.com/2017/09/seven-segment-led-display-controller-basys3-fpga.html

   2. https://www.fpga4student.com/2017/09/vhdl-code-for-seven-segment-display.html

   3. https://simple-circuit.com/pic18f46k22-7-segment-display-example/

   4. https://github.com/shahjui2000/Push-Button-Door-VHDL-

   5. https://www.kth.se/social/files/5458faeef276544021bdf437/codelockVHDL_eng.pdf

   6. https://github.com/fm4dd/pmod-7seg4

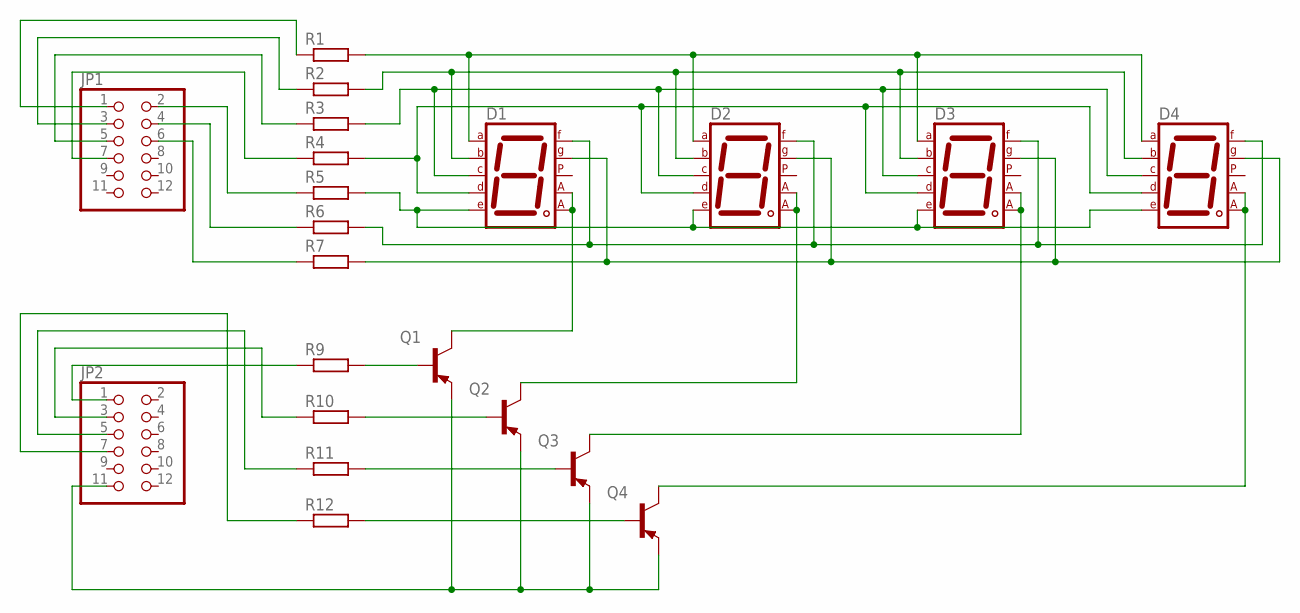
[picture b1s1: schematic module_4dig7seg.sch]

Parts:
D1, D2, D3, D4: 7SEG-CA; 7SEG-13
JP1, JP2: PINHD-2X6/90; 2X06/90
Q1, Q2, Q3, Q4: 2N3906; TO92
R1, R2, R3, R4, R5, R6, R7, R9, R10, R11, R12: R-EU_0204/7; 0204/7

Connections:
unnamed: Q1.2 (B), R9.2
unnamed: Q2.2 (B), R10.2
unnamed: Q3.2 (B), R11.2
unnamed: Q4.2 (B), R12.2
unnamed: JP2.7, R12.1
unnamed: JP2.1, R9.1
unnamed: JP2.3, R10.1
unnamed: JP2.5, R11.1
unnamed: JP2.11, Q1.3 (E), Q2.3 (E), Q3.3 (E), Q4.3 (E)
unnamed: JP1.7, R4.1
unnamed: JP1.5, R3.1
unnamed: JP1.3, R2.1
unnamed: JP1.1, R1.1
unnamed: JP1.2, R5.1
unnamed: JP1.4, R6.1
unnamed: JP1.6, R7.1
unnamed: D1.3 (CA1), D1.8 (CA2), Q1.1 (C)
unnamed: D1.7 (A), D2.7 (A), D3.7 (A), D4.7 (A), R1.2
unnamed: D3.3 (CA1), D3.8 (CA2), Q3.1 (C)
unnamed: D1.2 (D), D2.2 (D), D3.2 (D), D4.2 (D), R4.2
unnamed: D1.4 (C), D2.4 (C), D3.4 (C), D4.4 (C), R3.2
unnamed: D1.1 (E), D2.1 (E), D3.1 (E), D4.1 (E), R5.2
unnamed: D1.9 (F), D2.9 (F), D3.9 (F), D4.9 (F), R6.2
unnamed: D1.6 (B), D2.6 (B), D3.6 (B), D4.6 (B), R2.2
unnamed: D1.10 (G), D2.10 (G), D3.10 (G), D4.10 (G), R7.2
unnamed: D2.3 (CA1), D2.8 (CA2), Q2.1 (C)
unnamed: D4.3 (CA1), D4.8 (CA2), Q4.1 (C)

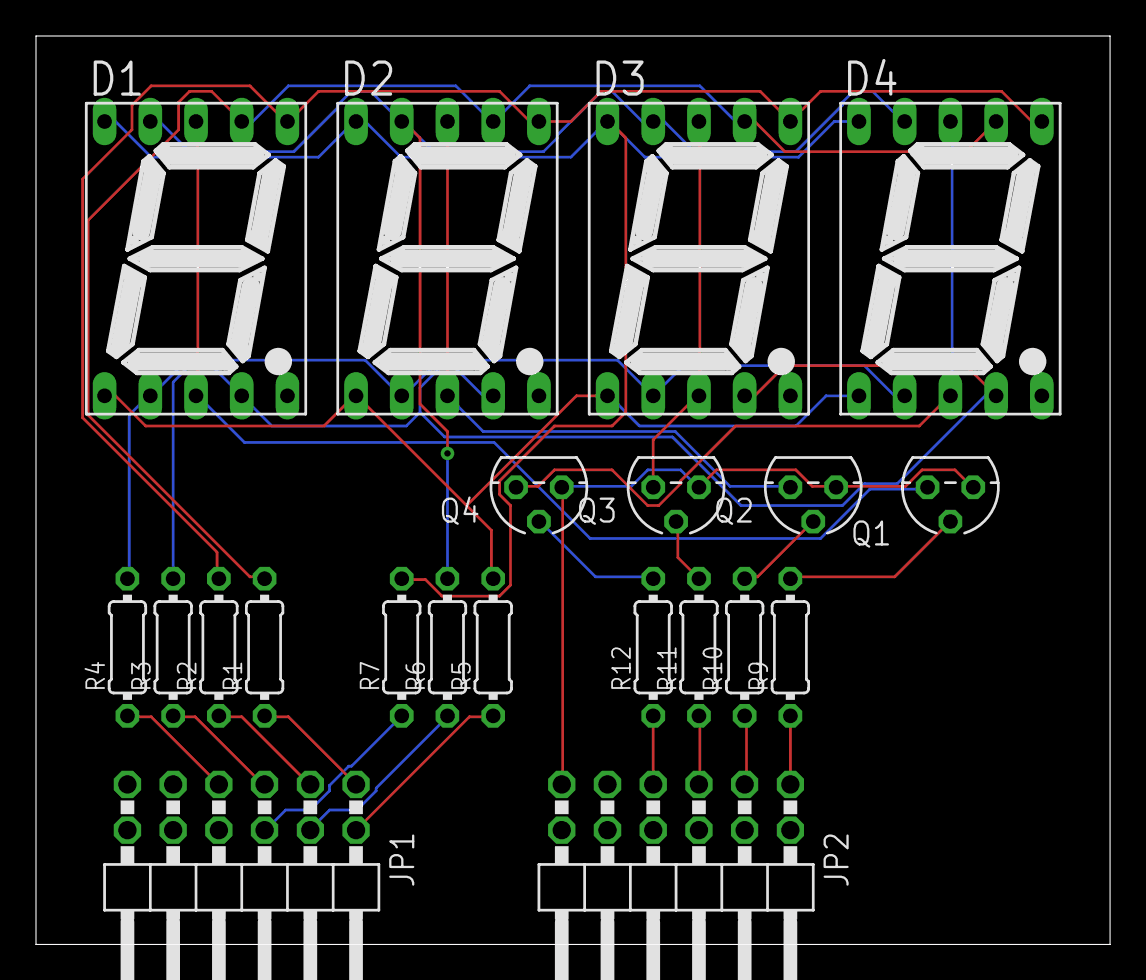
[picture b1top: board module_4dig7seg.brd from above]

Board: 2 copper layers, 59.7 x 50.5 mm, 21 parts (0 on the bottom side), 27 nets.

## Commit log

2021-02-13 1 commit
2021-02-13 DeMorgan Laws-image
2021-02-13 image reset
2021-02-13 dislaws png
2021-02-18 labs dir create
2021-02-19 Obrazky kmap
2021-02-19 zdruzeny obr kmap
2021-02-19 obrazky funkcii
2021-02-19 finalizing
2021-02-27 03vivado
2021-03-03 readme file update
2021-03-05 1st push
2021-03-07 almost final
2021-03-14 almost done
2021-03-14 final push
2021-03-17 making dir
2021-03-20 timing photo
2021-03-20 before constrain update
2021-03-20 lab done
2021-03-22 synch
2021-03-24 create
2021-03-24 reset
2021-03-29 syncg
2021-03-29 123 done
2021-03-29 final
2021-04-04 numero uno
2021-04-04 1,2 done
2021-04-04 done
2021-04-08 create project
2021-04-27 added 7seg_4dig
2021-04-27 Created folder Images
2021-04-27 Adde pictures
2021-04-27 added pictures
2021-04-27 added picture
2021-05-01 Added Table of contents
2021-05-02 Create tb_relay_to_door
2021-05-02 Rename tb_relay_to_door to tb_relay_to_door.vhd

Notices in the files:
Labs/Project/README.md:
-- Copyright (c) 2020 Tomas Fryza
-- This work is licensed under the terms of the MIT license.
-- Copyright (c) 2019-Present Tomas Fryza
